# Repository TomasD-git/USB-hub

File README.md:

# USB-hub
USB hub, has 2x usbc, 2x usba, with usbc as host

<details>
  <summary>BOM</summary>

| Name|Purpose|Quantity|Total Cost (USD)|Link|Distributor |  
| ----|-------|--------|----------------|----|----------- |
| PCB + stencil|all components are on this|1|12|https://jlcpcb.com|jlcpcb |  
| ALL components|all components that are on pcb|1|20|https://lcsc.com|lcsc|  
|  |  |  Total cost|32| | |  
  
</details>

<details>
  <summary>How to assemble</summary>

Buy a PCBA or solder yourself with hot air station or hotplate, place the assembled pcb into case and use m2 screws to screw it into place.  

</details>

# Pictures  

**Schematic**  
  
**PCB**  
  
**PCB (Back view)**  
  
**PCB (Front view)**  
  
**CAD (Back view)**  
  
**CAD (Front view)**

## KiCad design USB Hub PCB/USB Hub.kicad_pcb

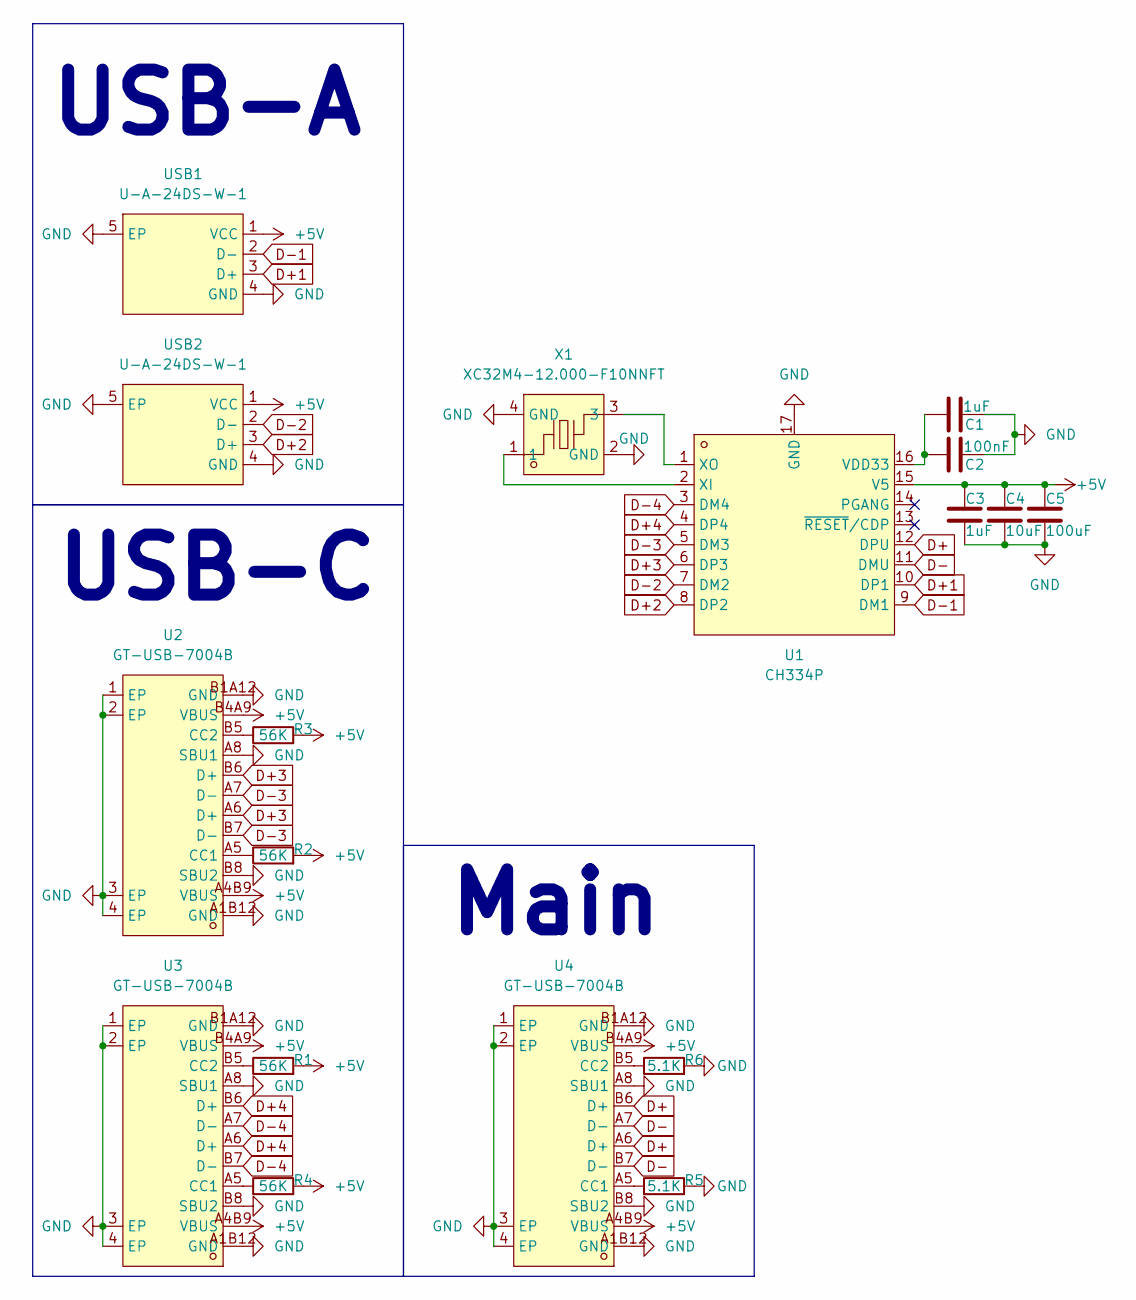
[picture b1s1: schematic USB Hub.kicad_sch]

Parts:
C1, C3: 1uF; C_0805_2012Metric_Pad1.18x1.45mm_HandSolder
C2: 100nF; C_0805_2012Metric_Pad1.18x1.45mm_HandSolder
C4: 10uF; C_1808_4520Metric_Pad1.72x2.30mm_HandSolder
C5: 100uF; C_1808_4520Metric_Pad1.72x2.30mm_HandSolder
R1, R2, R3, R4: 56K; R_1206_3216Metric_Pad1.30x1.75mm_HandSolder
R5, R6: 5.1K; R_1206_3216Metric_Pad1.30x1.75mm_HandSolder
U1: CH334P; QFN-16_L3.0-W3.0-P0.50-BL-EP1.7; MPN CH334P; LCSC Part C5373042
U2, U3, U4: GT-USB-7004B; USB-C-SMD_GT-USB-7004B; MPN GT-USB-7004B; LCSC Part C5368946
USB1, USB2: U-A-24DS-W-1; USB-A-SMD_U-A-24DS-W-2; MPN U-A-24DS-W-1; LCSC Part C530628
X1: XC32M4-12.000-F10NNFT; CRYSTAL-SMD_4P-L3.2-W2.5-BL; MPN XC32M4-12.000-F10NNFT; LCSC Part C2842186

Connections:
+5V: C3.2, C4.2, C5.2, R1.2, R2.2, R3.2, R4.2, U1.15 (V5), U2.A4B9 (VBUS), U2.B4A9 (VBUS), U3.A4B9 (VBUS), U3.B4A9 (VBUS), U4.A4B9 (VBUS), U4.B4A9 (VBUS), USB1.1 (VCC), USB2.1 (VCC)
D+: U1.12 (DPU), U4.A6 (D+), U4.B6 (D+)
D+1: U1.10 (DP1), USB1.3 (D+)
D+2: U1.8 (DP2), USB2.3 (D+)
D+3: U1.6 (DP3), U2.A6 (D+), U2.B6 (D+)
D+4: U1.4 (DP4), U3.A6 (D+), U3.B6 (D+)
D-: U1.11 (DMU), U4.A7 (D-), U4.B7 (D-)
D-1: U1.9 (DM1), USB1.2 (D-)
D-2: U1.7 (DM2), USB2.2 (D-)
D-3: U1.5 (DM3), U2.A7 (D-), U2.B7 (D-)
D-4: U1.3 (DM4), U3.A7 (D-), U3.B7 (D-)
GND: C1.2, C2.2, C3.1, C4.1, C5.1, R5.2, R6.2, U1.17 (GND), U2.1 (EP), U2.2 (EP), U2.3 (EP), U2.4 (EP), U2.A1B12 (GND), U2.A8 (SBU1), U2.B1A12 (GND), U2.B8 (SBU2), U3.1 (EP), U3.2 (EP), U3.3 (EP), U3.4 (EP), U3.A1B12 (GND), U3.A8 (SBU1), U3.B1A12 (GND), U3.B8 (SBU2), U4.1 (EP), U4.2 (EP), U4.3 (EP), U4.4 (EP), U4.A1B12 (GND), U4.A8 (SBU1), U4.B1A12 (GND), U4.B8 (SBU2), USB1.4 (GND), USB1.5 (EP), USB2.4 (GND), USB2.5 (EP), X1.2 (GND), X1.4 (GND)
unnamed: C1.1, C2.1, U1.16 (VDD33)
unnamed: U1.2 (XI), X1.1
unnamed: U1.1 (XO), X1.3
unnamed: R2.1, U2.A5 (CC1)
unnamed: R3.1, U2.B5 (CC2)
unnamed: R4.1, U3.A5 (CC1)
unnamed: R1.1, U3.B5 (CC2)
unnamed: R5.1, U4.A5 (CC1)
unnamed: R6.1, U4.B5 (CC2)

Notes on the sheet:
USB-A
Main
USB-C

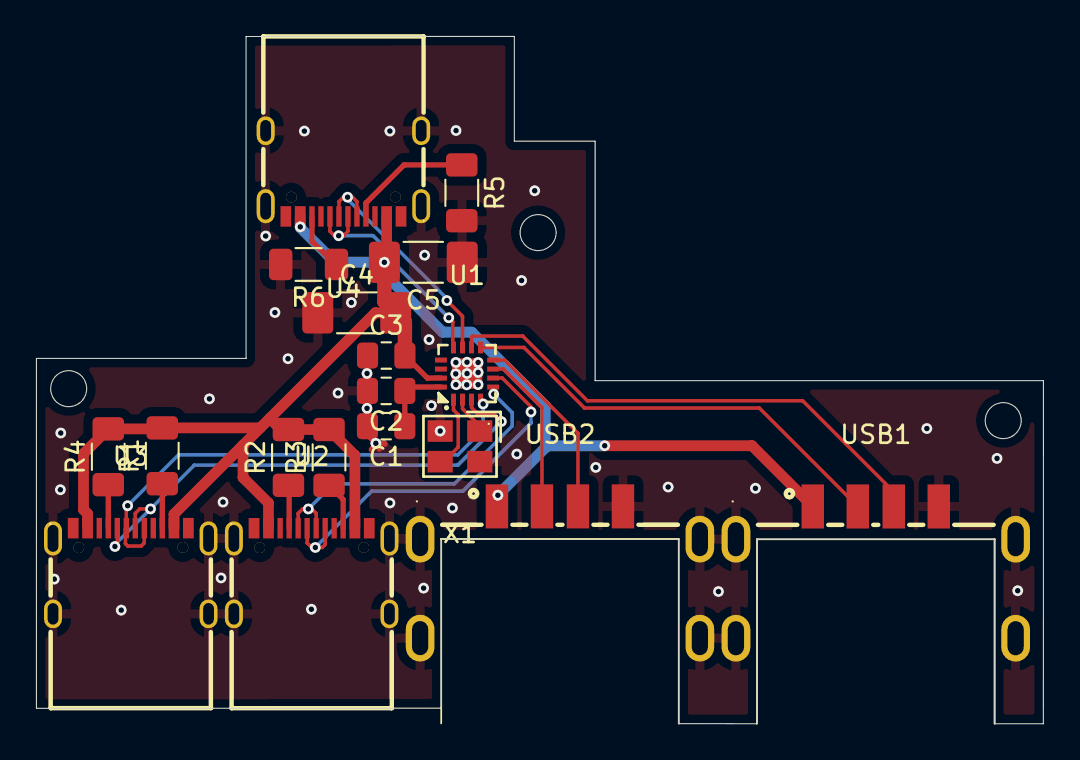
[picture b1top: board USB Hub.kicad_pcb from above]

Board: 2 copper layers, 55.9 x 38.2 mm, 18 parts (0 on the bottom side), 21 nets.

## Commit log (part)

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2026-06-23 added PCB files
2026-06-23 adde BOM
2026-06-23 added CAD files
